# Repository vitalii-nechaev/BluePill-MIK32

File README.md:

# BluePill-MIK32
Проект отладочной платы MIK32 АМУР К1948ВК018, выполненный в среде KiCad.   
В папке КД находятся pdf-файлы документации на плату. Текстовые документы сгенерированы в программе [ДокГОСТ](https://github.com/vitalii-nechaev/DocGOST).  
Подробнее с проектом можно ознакомиться на [странице проекта](http://xn-----6kccalfmhwcdcrbm1aajnghfrqjce3b0z.xn--p1ai/MCU/MIK32_devboard.html).

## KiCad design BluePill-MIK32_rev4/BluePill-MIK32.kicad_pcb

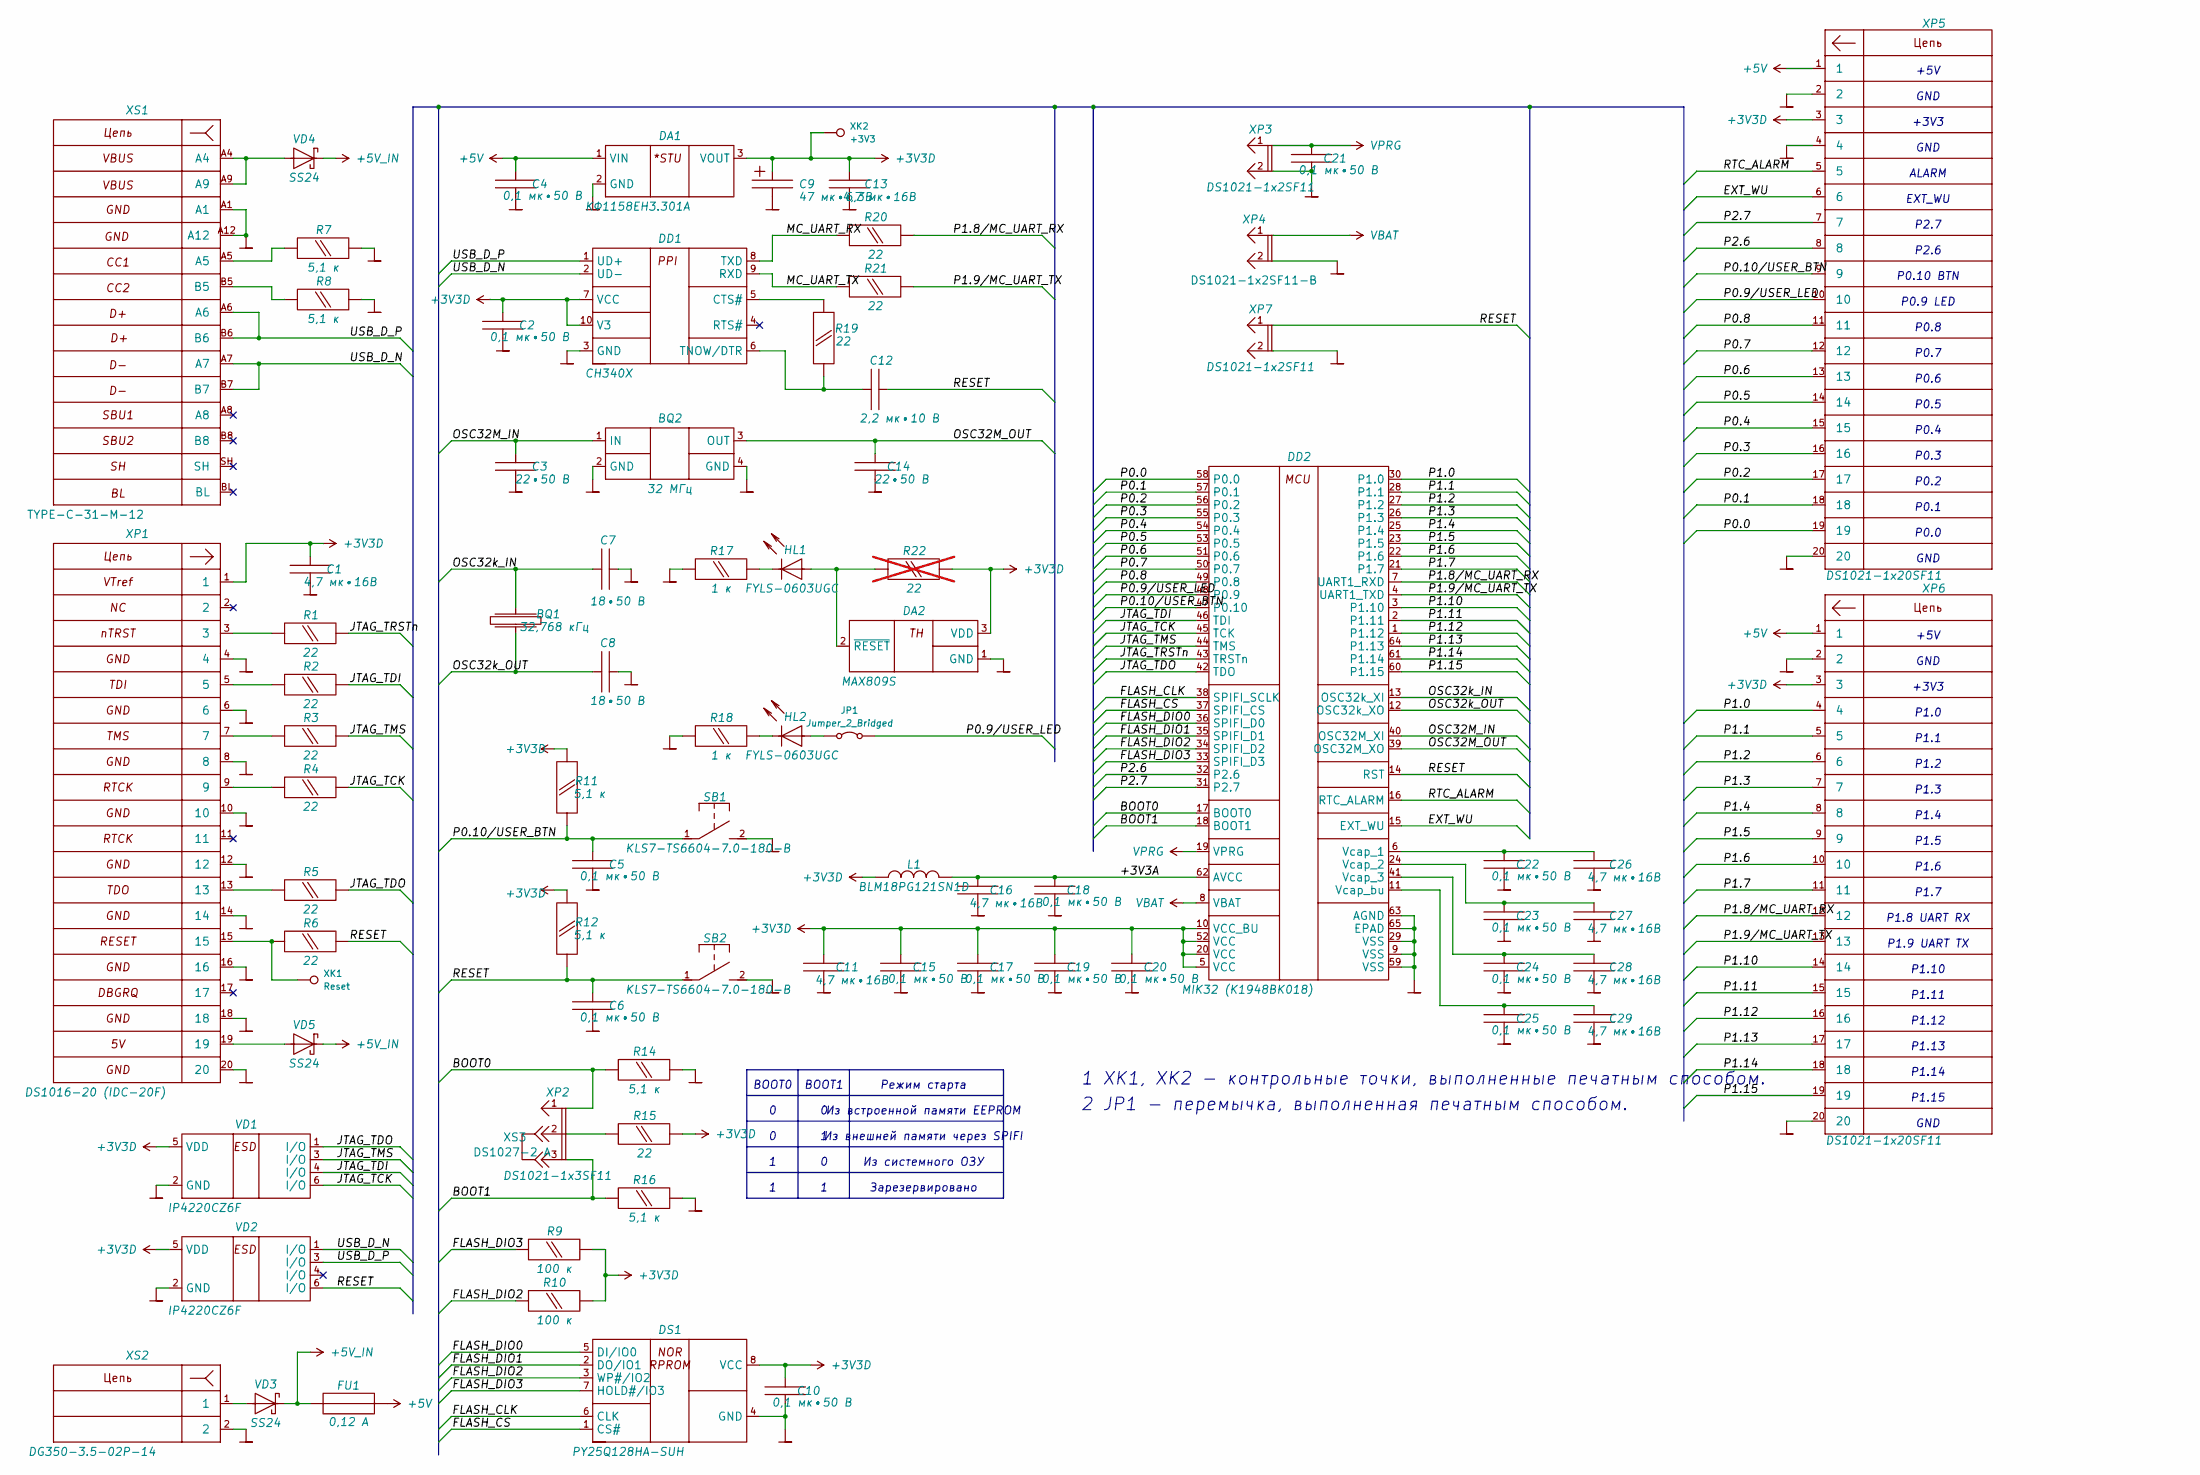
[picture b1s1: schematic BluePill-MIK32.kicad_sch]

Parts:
BQ1: 32,768 кГц; Crystal_SMD_3215-2Pin_3.2x1.5mm; PartNumber X321532768KGD2SI
BQ2: 32 МГц; Crystal_SMD_3225-4Pin_3.2x2.5mm; PartNumber X322532MOB4SI
C1, C11, C13, C16, C26, C27, C28, C29: 4,7 мк•16В; C_0603_1608Metric; PartNumber GRM188R61C475KE11D
C2, C4, C5, C6, C10, C15, C17, C18, C19, C20, C21, C22, C23, C24, C25: 0,1 мк•50 В; C_0402_1005Metric; PartNumber GRM155R71H104KE14D
C3, C14: 22•50 В; C_0402_1005Metric; PartNumber GRM1555C1H220JA01D
C7, C8: 18•50 В; C_0402_1005Metric; PartNumber GRM1555C1E180JA01D
C9: 47 мк•6,3В; CP_Radial_D5mm_P2.5mm_H11mm; PartNumber К50-68-6,3В-47мкФ±20%
C12: 2,2 мк•10 В; C_0402_1005Metric; PartNumber GRM155R61A225KE01D
DA1: КФ1158ЕН3.301А; TO-252-2; PartNumber КФ1158ЕН3.301А
DA2: MAX809S; SOT-23; PartNumber MAX809S
DD1: CH340X; MSOP-10_3x3mm_P0.5mm; PartNumber CH340X
DD2: MIK32 (К1948ВК018); QFN-64-1EP_8x8mm_P0.4mm_EP6.5x6.5mm; PartNumber К1948ВК018
DS1: PY25Q128HA-SUH; SOIC-8_5.23x5.23mm_P1.27mm; PartNumber PY25Q128HA-SUH
FU1: 0,12 А; Fuse_1206_3216Metric; PartNumber FSMD012-1206-R
HL1, HL2: FYLS-0603UGC; LED_0603_1608Metric; PartNumber FYLS-0603UGC
JP1: Jumper_2_Bridged; SolderJumper-2_P1.3mm_Bridged_RoundedPad1.0x1.5mm
L1: BLM18PG121SN1D; L_0603_1608Metric; PartNumber BLM18PG121SN1D
R1, R2, R3, R4, R5, R6, R15, R19, R20, R21: 22; R_0603_1608Metric; PartNumber RC0603JR-0722RL
R7, R8, R11, R12, R14, R16: 5,1 к; R_0603_1608Metric; PartNumber RC0603FR-075K1L
R9, R10: 100 к; R_0603_1608Metric; PartNumber RC0603JR-07100KL
R17, R18: 1 к; R_0603_1608Metric; PartNumber RC0603JR-071KL
R22: 22; R_0603_1608Metric; PartNumber RC0603JR-0722RL; not fitted
SB1, SB2: KLS7-TS6604-7.0-180-B; SW_Push_1P1T_NO_6x6mm_H9.5mm; PartNumber KLS7-TS6604-7.0-180-B
VD1, VD2: IP4220CZ6F; SOT-23-6; PartNumber IP4220CZ6
VD3, VD4, VD5: SS24; DO-214AC(SMA); PartNumber SS24
XK1: Reset; TestPoint_THTPad_D2.0mm_Drill1.0mm
XK2: +3V3; TestPoint_THTPad_D2.0mm_Drill1.0mm
XP1: DS1016-20 (IDC-20F); IDC-Header_2x10_P2.54mm_Vertical; PartNumber DS1016-20 (IDC-20F)
XP2: DS1021-1x3SF11; PinHeader_1x03_P2.54mm_Vertical; PartNumber DS1021-1x3SF11
XP3, XP7: DS1021-1x2SF11; PinHeader_1x02_P2.54mm_Vertical; PartNumber DS1021-1x2SF11
XP4: DS1021-1x2SF11-B; PinHeader_1x02_P2.54mm_Vertical; PartNumber DS1021-1x2SF11-B
XP5, XP6: DS1021-1x20SF11; PinHeader_1x20_P2.54mm_Vertical; PartNumber DS1021-1x20SF11
XS1: TYPE-C-31-M-12; USB_C_Receptacle_16P_TopMnt_Horizontal; PartNumber TYPE-C-31-M-12
XS2: DG350-3.5-02P-14; TerminalBlock_1x02_P3.50mm_Horizontal; PartNumber DG350-3.5-02P-14
XS3: DS1027-2 A; PartNumber DS1027-2 A

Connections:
+3V3D: C1.1, C2.1, C9.1, C10.1, C11.1, C13.1, C15.1, C17.1, C19.1, C20.1, DA1.3 (VOUT), DA2.3 (VDD), DD1.7 (VCC), DD1.10 (V3), DD2.5 (VCC), DD2.10 (VCC_BU), DD2.20 (VCC), DD2.52 (VCC), DS1.8 (VCC), L1.1, R9.2, R10.2, R11.2, R12.2, R15.2, R22.2, VD1.5 (VDD), VD2.5 (VDD), XK2.1, XP1.1, XP5.3, XP6.3
+5V: C4.1, DA1.1 (VIN), FU1.2, XP5.1, XP6.1
+5V_IN: FU1.1, VD3.1 (K), VD4.1 (K), VD5.1 (K)
/+3V3A: C16.1, C18.1, DD2.62 (AVCC), L1.2
/BOOT0: DD2.17 (BOOT0), R14.1, XP2.1
/BOOT1: DD2.18 (BOOT1), R16.1, XP2.3
/EXT_WU: DD2.15 (EXT_WU), XP5.6
/FLASH_CLK: DD2.38 (SPIFI_SCLK), DS1.6 (CLK)
/FLASH_CS: DD2.37 (SPIFI_CS), DS1.1 (CS#)
/FLASH_DIO0: DD2.36 (SPIFI_D0), DS1.5 (DI/IO0)
/FLASH_DIO1: DD2.35 (SPIFI_D1), DS1.2 (DO/IO1)
/FLASH_DIO2: DD2.34 (SPIFI_D2), DS1.3 (WP#/IO2), R10.1
/FLASH_DIO3: DD2.33 (SPIFI_D3), DS1.7 (HOLD#/IO3), R9.1
/JTAG_TCK: DD2.45 (TCK), R4.2, VD1.6 (I/O)
/JTAG_TDI: DD2.46 (TDI), R2.2, VD1.4 (I/O)
/JTAG_TDO: DD2.42 (TDO), R5.2, VD1.1 (I/O)
/JTAG_TMS: DD2.44 (TMS), R3.2, VD1.3 (I/O)
/JTAG_TRSTn: DD2.43 (TRSTn), R1.2
/MC_UART_RX: DD1.8 (TXD), R20.1
/MC_UART_TX: DD1.9 (RXD), R21.1
/OSC32M_IN: BQ2.1 (IN), C3.1, DD2.40 (OSC32M_XI)
/OSC32M_OUT: BQ2.3 (OUT), C14.1, DD2.39 (OSC32M_XO)
/OSC32k_IN: BQ1.2, C7.1, DD2.13 (OSC32k_XI)
/OSC32k_OUT: BQ1.1, C8.1, DD2.12 (OSC32k_XO)
/P0.0: DD2.58 (P0.0), XP5.19
/P0.1: DD2.57 (P0.1), XP5.18
/P0.2: DD2.56 (P0.2), XP5.17
/P0.3: DD2.55 (P0.3), XP5.16
/P0.4: DD2.54 (P0.4), XP5.15
/P0.5: DD2.53 (P0.5), XP5.14
/P0.6: DD2.51 (P0.6), XP5.13
/P0.7: DD2.50 (P0.7), XP5.12
/P0.8: DD2.49 (P0.8), XP5.11
/P0.9/USER_LED: DD2.48 (P0.9), JP1.2 (B), XP5.10
/P0.10/USER_BTN: C5.1, DD2.47 (P0.10), R11.1, SB1.1, XP5.9
/P1.0: DD2.30 (P1.0), XP6.4
/P1.1: DD2.28 (P1.1), XP6.5
/P1.2: DD2.27 (P1.2), XP6.6
/P1.3: DD2.26 (P1.3), XP6.7
/P1.4: DD2.25 (P1.4), XP6.8
/P1.5: DD2.23 (P1.5), XP6.9
/P1.6: DD2.22 (P1.6), XP6.10
/P1.7: DD2.21 (P1.7), XP6.11
/P1.8/MC_UART_RX: DD2.7 (UART1_RXD), R20.2, XP6.12
/P1.9/MC_UART_TX: DD2.4 (UART1_TXD), R21.2, XP6.13
/P1.10: DD2.3 (P1.10), XP6.14
/P1.11: DD2.2 (P1.11), XP6.15
/P1.12: DD2.1 (P1.12), XP6.16
/P1.13: DD2.64 (P1.13), XP6.17
/P1.14: DD2.61 (P1.14), XP6.18
/P1.15: DD2.60 (P1.15), XP6.19
/P2.6: DD2.32 (P2.6), XP5.8
/P2.7: DD2.31 (P2.7), XP5.7
/RESET: C6.1, C12.2, DD2.14 (RST), R6.2, R12.1, SB2.1, VD2.6 (I/O), XP7.1
/RTC_ALARM: DD2.16 (RTC_ALARM), XP5.5
/USB_D_N: DD1.2 (UD-), VD2.1 (I/O), XS1.A7, XS1.B7
/USB_D_P: DD1.1 (UD+), VD2.3 (I/O), XS1.A6, XS1.B6
GND: BQ2.2 (GND), BQ2.4 (GND), C1.2, C2.2, C3.2, C4.2, C5.2, C6.2, C7.2, C8.2, C9.2, C10.2, C11.2, C13.2, C14.2, C15.2, C16.2, C17.2, C18.2, C19.2, C20.2, C21.2, C22.2, C23.2, C24.2, C25.2, C26.2, C27.2, C28.2, C29.2, DA1.2 (GND), DA2.1 (GND), DD1.3 (GND), DD2.9 (VSS), DD2.29 (VSS), DD2.59 (VSS), DD2.63 (AGND), DD2.65 (EPAD), DS1.4 (GND), R7.2, R8.2, R14.2, R16.2, R17.1, R18.1, SB1.2, SB2.2, VD1.2 (GND), VD2.2 (GND), XP1.4, XP1.6, XP1.8, XP1.10, XP1.12, XP1.14, XP1.16, XP1.18, XP1.20, XP3.2, XP4.2, XP5.2, XP5.4, XP5.20, XP6.2, XP6.20, XP7.2, XS1.A1, XS1.A12, XS2.2
unnamed: DA2.2 (~RESET), HL1.2 (A), R22.1
unnamed: DD1.5 (CTS#), R19.2
unnamed: C12.1, DD1.6 (TNOW/DTR), R19.1
unnamed: C22.1, C26.1, DD2.6 (Vcap_1)
unnamed: C23.1, C27.1, DD2.24 (Vcap_2)
unnamed: C24.1, C28.1, DD2.41 (Vcap_3)
unnamed: C25.1, C29.1, DD2.11 (Vcap_bu)
unnamed: HL1.1 (K), R17.2
unnamed: HL2.2 (A), JP1.1 (A)
unnamed: HL2.1 (K), R18.2
unnamed: R1.1, XP1.3
unnamed: R2.1, XP1.5
unnamed: R3.1, XP1.7
unnamed: R4.1, XP1.9
unnamed: R5.1, XP1.13
unnamed: R6.1, XK1.1, XP1.15
unnamed: R7.1, XS1.A5
unnamed: R8.1, XS1.B5
unnamed: R15.1, XP2.2
unnamed: VD3.2 (A), XS2.1
unnamed: VD4.2 (A), XS1.A4, XS1.A9
unnamed: VD5.2 (A), XP1.19
VBAT: DD2.8 (VBAT), XP4.1
VPRG: C21.1, DD2.19 (VPRG), XP3.1

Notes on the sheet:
P1.0
+5V
P1.2
GND
EXT_WU
BOOT1
Режим старта
P1.5
P1.8 UART RX
2 JP1 - перемычка, выполненная печатным способом.
P0.1
P1.1
Из системного ОЗУ
P1.11
P1.15
P1.6
P1.7
P0.2
P1.9 UART TX
Из внешней памяти через SPIFI
P0.10 BTN
P0.4
P1.14
ALARM
P2.6
P0.7
1 XK1, XK2 - контрольные точки, выполненные печатным способом.
P2.7
P1.12
P1.10
Зарезервировано
P0.9 LED
P0.8
P0.0
P0.5
BOOT0
Из встроенной памяти EEPROM
P1.13
P0.3
P1.4

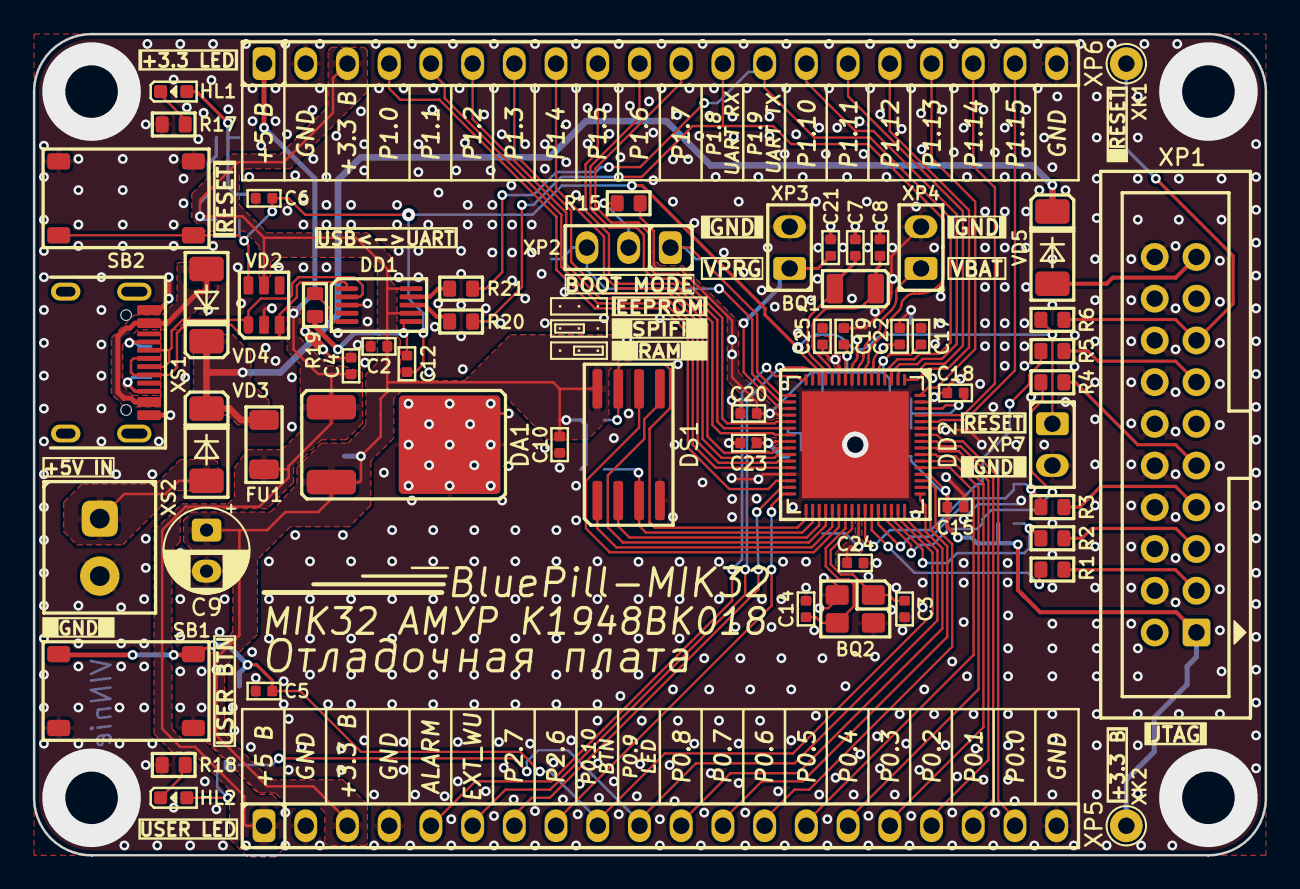
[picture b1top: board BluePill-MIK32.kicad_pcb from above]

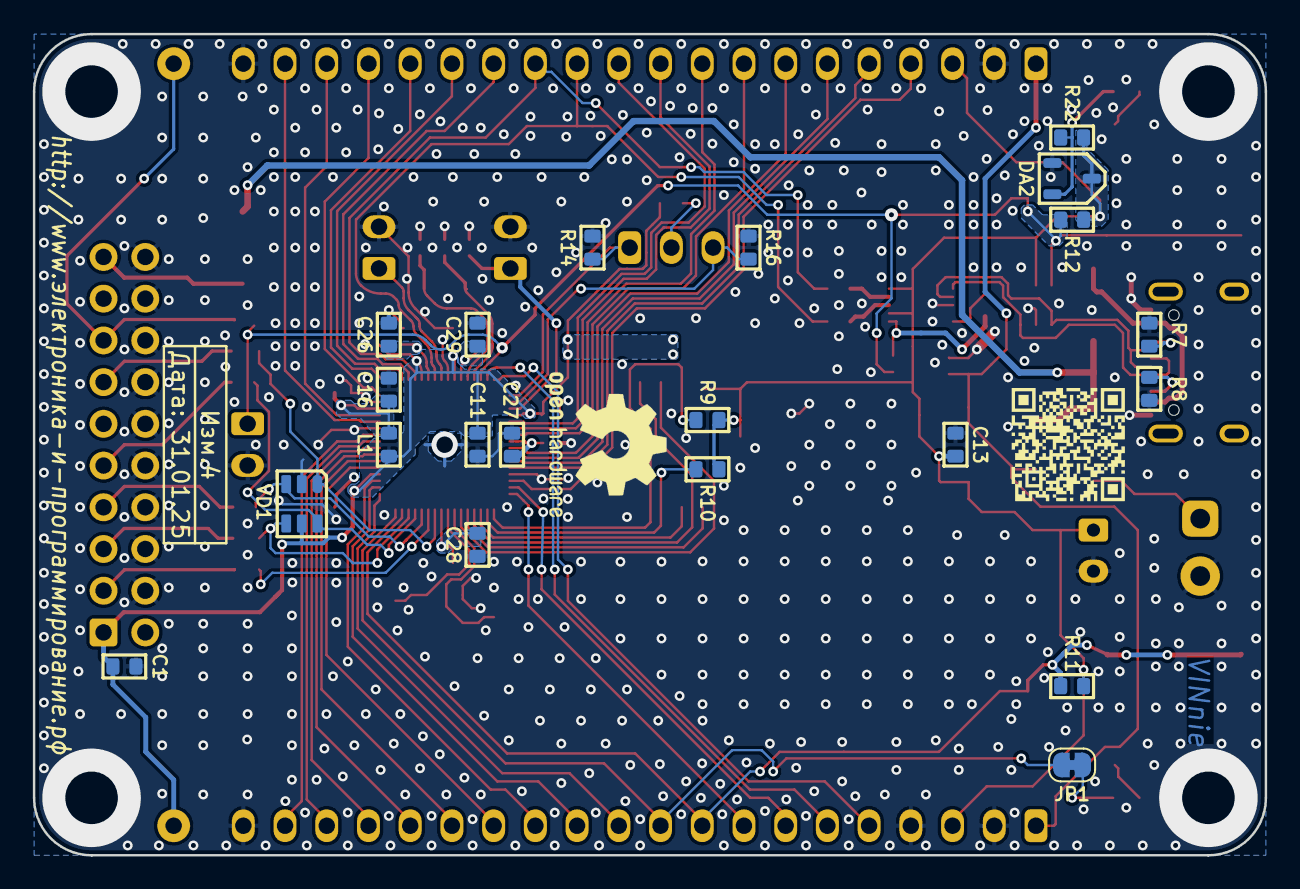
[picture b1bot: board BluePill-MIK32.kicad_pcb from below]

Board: 2 copper layers, 75.0 x 50.0 mm, 80 parts (21 on the bottom side), 82 nets.

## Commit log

2024-12-25 Create BluePill-MIK32_rev3
2024-12-25 rev3
